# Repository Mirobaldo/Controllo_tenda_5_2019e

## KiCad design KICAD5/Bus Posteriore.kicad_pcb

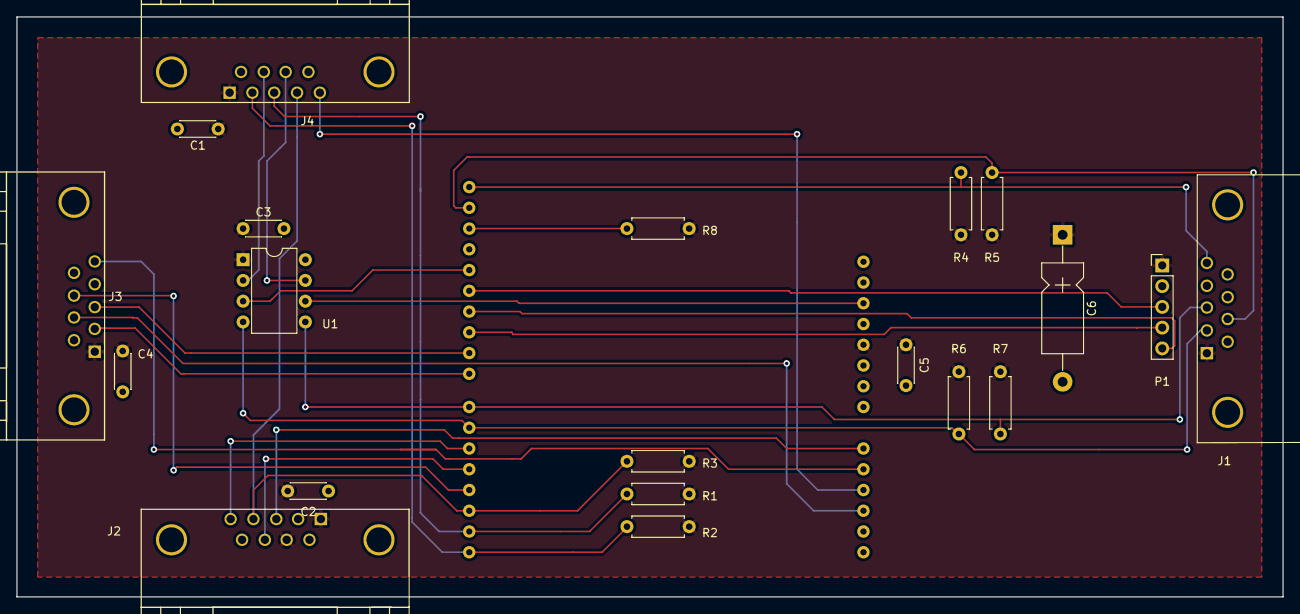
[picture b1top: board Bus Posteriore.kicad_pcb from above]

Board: 2 copper layers, 155.0 x 71.0 mm, 21 parts (1 on the bottom side), 26 nets.

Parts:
C1, C2, C3, C4, C5: 100nF; C_Disc_D4.3mm_W1.9mm_P5.00mm
C6: 100uF; CP_Axial_L11.0mm_D5.0mm_P18.00mm_Horizontal
J1: DB9; DB9MC
J2, J3, J4: DB9; DB9FCsmall
P1: CONN_01X05; Pin_Header_Straight_1x05_Pitch2.54mm
R1, R2, R3, R4, R5, R6, R7: 10kR; R_Axial_DIN0207_L6.3mm_D2.5mm_P7.62mm_Horizontal
R8: 100R; R_Axial_DIN0207_L6.3mm_D2.5mm_P7.62mm_Horizontal
SH1: ARDUINO_as_UNO; ARDUINO_as_UNO_R3_CONTOUR
U1: PIC12F675-I/P; DIP-8_W7.62mm

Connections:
+5V: C1.1, C2.1, C3.1, C4.1, C5.1, C6.1, J1.1, J2.1, J2.7, J3.1, J4.1, P1.1, R1.1, R2.1, R3.1, R4.1, R5.1, R6.1, R7.1, R8.1, SH1.5V, U1.1
/DHTdata: J2.5, SH1.5
/DispClock: P1.5, SH1.11
/DispData: P1.3, SH1.12
/DispLoad: P1.4, SH1.10
/Pin2: J2.4, J4.4, R3.2, SH1.2
/PosReed: J2.8, SH1.4
/RX: J4.2, R2.2, SH1.0
/SCL: J1.5, R4.2, SH1.A5/2
/SDA: J1.7, R5.2, SH1.A4/2
/SP1: J4.8, U1.7
/SP2: J4.7, U1.2
/TX: J4.3, R1.2, SH1.1
/WDPulse: SH1.13, U1.3
/WDReset: SH1.RST, U1.6
/WindSwitch: J3.8, SH1.3
/Zero: J2.3, SH1.A0
/cmdSBOpen: J3.2, SH1.8
/cmdSBclose: J3.3, SH1.9
/psbSBClose: J1.3, R7.2, SH1.7, U1.5
/psbSBOpen: J1.2, R6.2, SH1.6, U1.4
/swEndRun: J3.7, SH1.A3
GND: C1.2, C2.2, C3.2, C4.2, C5.2, C6.2, J1.6, J1.9, J2.2, J2.6, J2.9, J3.6, J3.9, J4.6, J4.9, P1.2, SH1.GND1, SH1.GND2, SH1.GND3, U1.8
unnamed: J3.5, SH1.A1
unnamed: J4.5, SH1.A2
unnamed: R8.2, SH1.AREF

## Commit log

2021-07-19 210719a Primo commit master
